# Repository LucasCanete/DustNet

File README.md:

# DustNet
Dust Measuring Station - Hochschule Osnabrück/Metropolia University

## Design Targets

Below is a list of circuits/features the schematic should include, regardless of if they are
part of the final design. 

The following [spreadsheet](https://docs.google.com/spreadsheets/d/1nFCJ1y3GU6Kr_cr4SUHvQ15Shn2fzcA_q6WiAYg45g8/edit?gid=0#gid=0)
is used to track some of the larger active components that are part of the electrical design.

- Battery cell (holder, connector)
- Cell Protection Circuit
- Cell Management Circuit (with MPPT)
- 3V3 Power rail
- Lora Powergate (res. GPIO + N-MOSFET)

## Final Design Circuits

TBD

## BOM

TBD

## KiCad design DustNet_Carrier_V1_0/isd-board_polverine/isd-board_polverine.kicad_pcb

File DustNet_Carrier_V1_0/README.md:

# DustNet
Dust Measuring Station - Hochschule Osnabrück/Metropolia University

## Board Features

- Dual-socket for Polverine and DFR1117 (mutually excl.)
- LiPo Protection Circuit
- 5V Power
- MPPT for charging
- USB-C for charging
- BME690 footprint (I2C)
- BMV080 connector (I2C)
- SPS30 connector (I2C)

## BOM

TBD

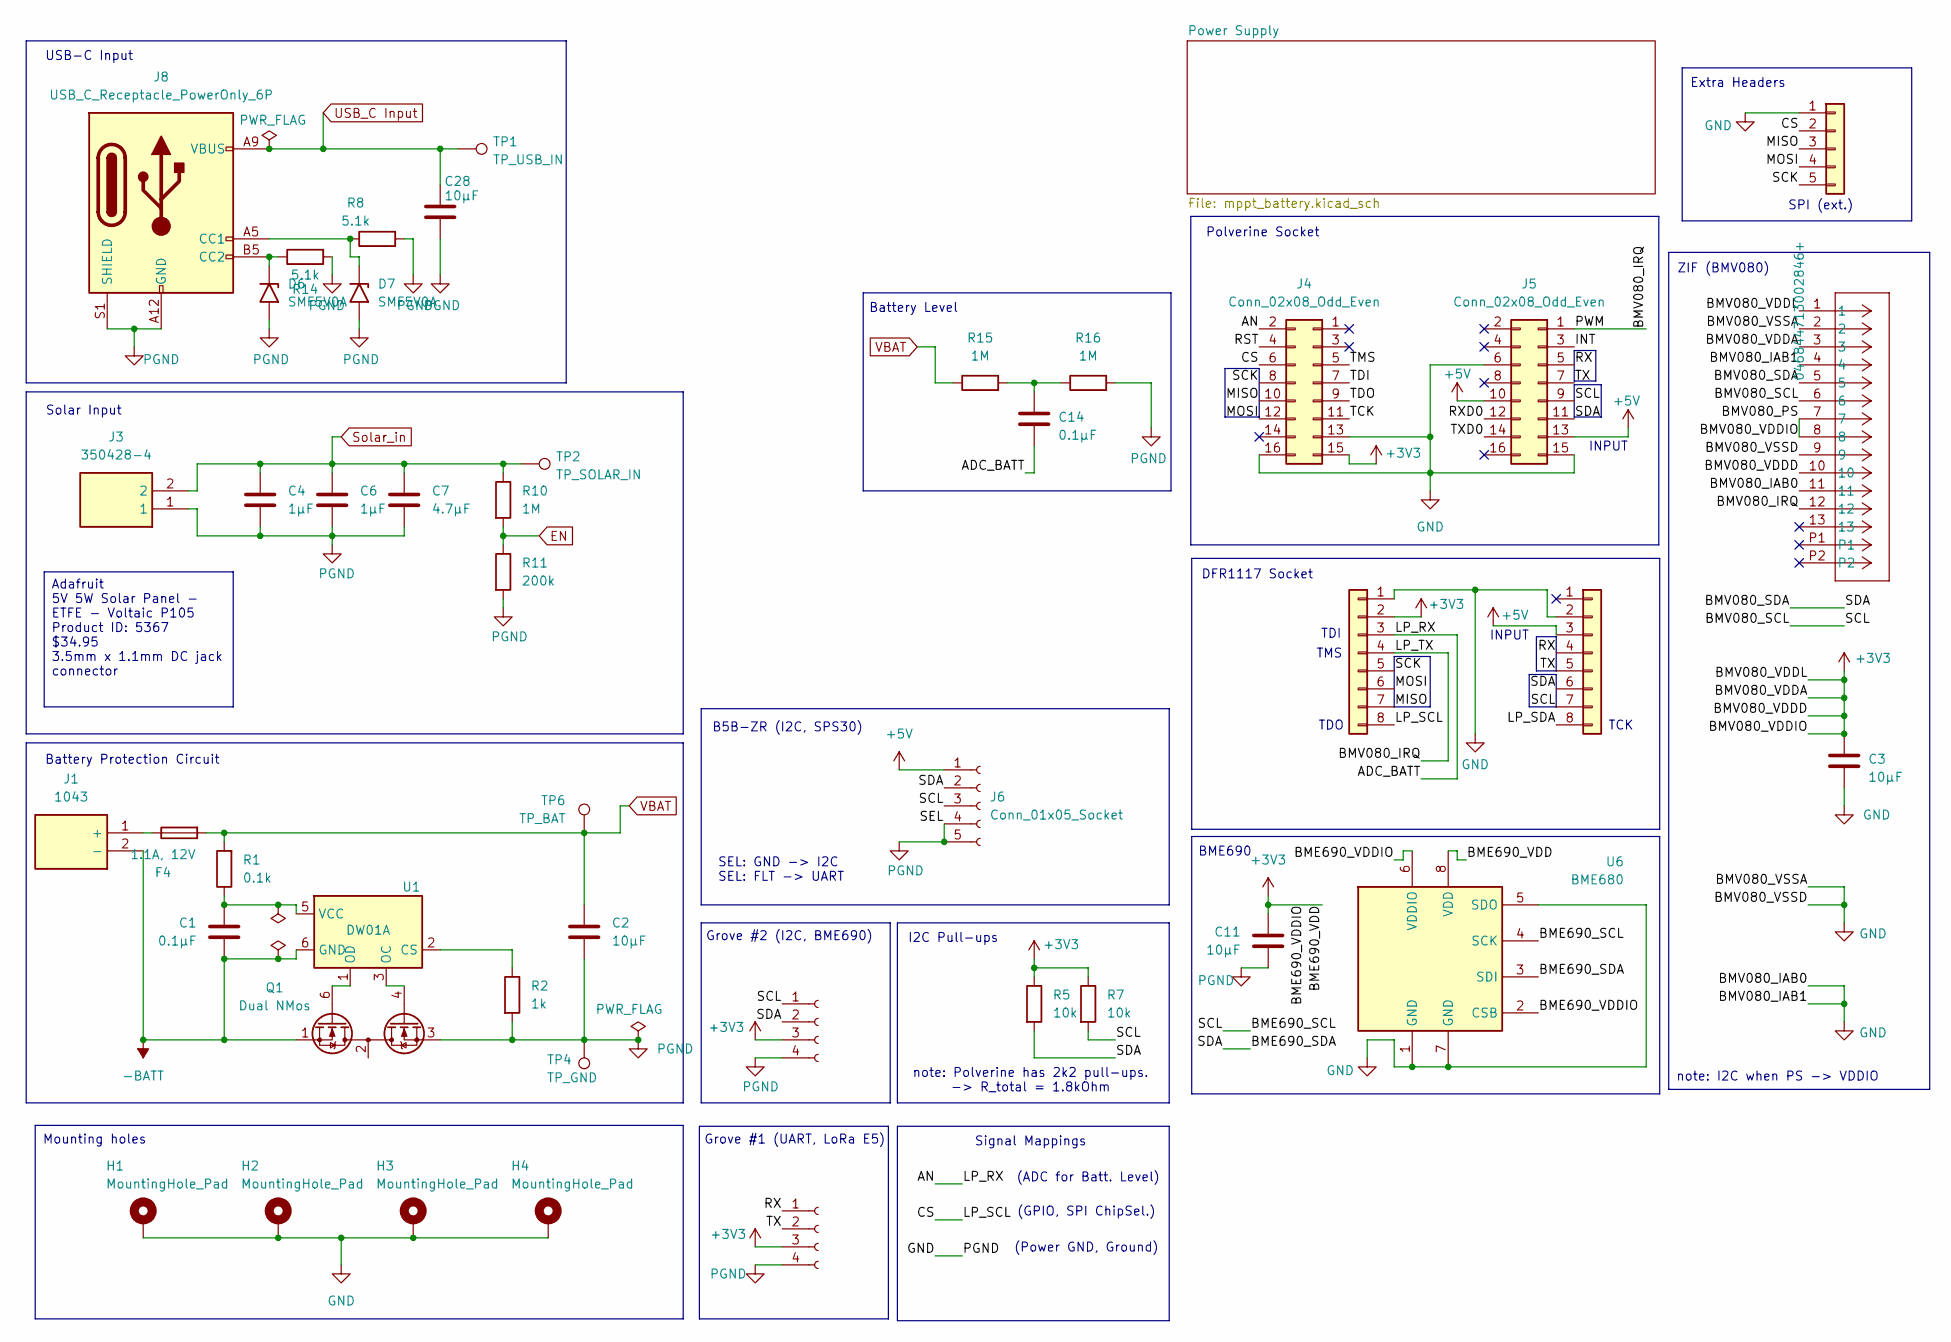
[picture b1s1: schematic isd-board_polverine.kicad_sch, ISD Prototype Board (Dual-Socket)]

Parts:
C1, C14: 0.1µF; C_0603_1608Metric; MPN 399-C0805C104K5RACTUCT-ND
C2, C3, C11: 10µF; C_0603_1608Metric; MPN GRM21BR61E106KA73K
C4, C6: 1µF; C_0603_1608Metric
C7: 4.7µF; C_0603_1608Metric
C28: 10µF; C_0603_1608Metric
D6, D7: SMF5V0A; D_SMF
F4: 1.1A, 12V; Fuse_1210_3225Metric_Pad1.42x2.65mm_HandSolder; MPN SMD1210B110TF
H1, H2, H3, H4: MountingHole_Pad; MountingHole_2.5mm_Pad_Via; MPN none
J1: 1043; Mouser Part Number 534-1043
J2, J9: Conn_01x04_Socket; NS-Tech_Grove_1x04_P2mm_Vertical; MPN 1597-1082-ND
J3: 350428-4; 3504284; Mouser Part Number 571-350428-4
J4, J5: Conn_02x08_Odd_Even; PinSocket_2x08_P2.54mm_Vertical; MPN 732-61301621821-ND
J6: Conn_01x05_Socket; JST_ZH_B5B-ZR_1x05_P1.50mm_Vertical; MPN B5B-ZR
J7, J10: Conn_01x08; PinSocket_1x08_P2.54mm_Vertical; MPN PPTC081LFBN-RC
J8: USB_C_Receptacle_PowerOnly_6P; USB_C_Receptacle_GCT_USB4125-xx-x-0190_6P_TopMnt_Horizontal; MPN USB4125-GF-A
J12: 5035661302; CON_5035661302_MOL; MPN 046844713002846+
J13: Conn_01x05; PinHeader_1x05_P2.54mm_Vertical; MPN ???
Q1: Dual NMos; SOT-23-6; MPN DMG9926UDMDICT-ND
R1: 0.1k; R_0603_1608Metric; MPN 541-100CCT-ND
R2: 1k; R_0603_1608Metric; MPN 10-ERJ-HP6J102VCT-ND
R5, R7: 10k; R_0603_1608Metric; MPN 541-4163-1-ND
R8, R14: 5.1k; R_0603_1608Metric; MPN 311-5.1KARCT-ND
R10: 1M; R_0603_1608Metric
R11: 200k; R_0603_1608Metric
R15, R16: 1M; R_0603_1608Metric; MPN 408-RG2012P-105-B-T5CT-ND
TP1: TP_USB_IN; TestPoint_Pad_1.5x1.5mm; MPN none
TP2: TP_SOLAR_IN; TestPoint_Pad_1.5x1.5mm; MPN none
TP4: TP_GND; TestPoint_Pad_D1.0mm; MPN none
TP6: TP_BAT; TestPoint_Pad_1.5x1.5mm; MPN none
U1: DW01A; SOT-23-6_Handsoldering; MPN DW01A
U6: BME680; Bosch_LGA-8_3x3mm_P0.8mm_ClockwisePinNumbering; MPN BME690

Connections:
+3V3: C3.1, C11.1, J2.3, J4.15, J9.3, J10.2, J12.1, J12.3, J12.7, J12.8, J12.10, R5.1, R7.1, U6.2 (CSB), U6.6 (VDDIO), U6.8 (VDD); also elsewhere on the board
+5V: J5.10, J5.13, J6.1, J7.3; also elsewhere on the board
-BATT: C1.2, J1.2 (-), Q1.1 (D1), U1.6 (GND)
/ADC_BATT: C14.2, J4.2, J10.3
/BME690_SCL: J2.1, J5.9, J6.3, J7.7, J12.6, R7.2, U6.4 (SCK)
/BME690_SDA: J2.2, J5.11, J6.2, J7.6, J12.5, R5.2, U6.3 (SDI)
/BMV080_IRQ: J5.1, J10.4, J12.12
/CS: J4.6, J10.8, J13.2
/INT: J5.3
/LP_SDA: J7.8
/MISO: J4.10, J10.7, J13.3
/MOSI: J4.12, J10.6, J13.4
/RST: J4.4
/RX: J5.5, J7.4, J9.1
/RXD0: J5.12
/SCK: J4.8, J10.5, J13.5
/TCK: J4.11
/TDI: J4.7
/TDO: J4.9
/TMS: J4.5
/TX: J5.7, J7.5, J9.2
/TXD0: J5.14
EN: R10.2, R11.1; also elsewhere on the board
unnamed: C14.1, R15.2, R16.1
unnamed: D6.1 (A1), J8.B5 (CC2), R14.1
unnamed: D7.1 (A1), J8.A5 (CC1), R8.1
unnamed: F4.1, J1.1 (+)
unnamed: Q1.6 (G1), U1.1 (OD)
unnamed: Q1.4 (G2), U1.3 (OC)
unnamed: Q1.2 (S1/D2), Q1.5 (S1/D2)
unnamed: R2.1, U1.2 (CS)
unnamed: C1.1, R1.1, U1.5 (VCC)
Solar_in: C4.1, C6.1, C7.1, J3.2, R10.1, TP2.1; also elsewhere on the board
USB_C Input: C28.1, J8.A9 (VBUS), J8.B9 (VBUS), TP1.1; also elsewhere on the board
VBAT: C2.1, F4.2, R1.2, R15.1, TP6.1; also elsewhere on the board

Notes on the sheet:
INPUT
B5B-ZR (I2C, SPS30)
Polverine Socket
TDO
I2C Pull-ups
Battery Level
note: Polverine has 2k2 pull-ups. -> R_total = 1.8kOhm
Solar Input
DFR1117 Socket
Mounting holes
TDI
BME690
(GPIO, SPI ChipSel.)
TCK
Extra Headers
(ADC for Batt. Level)
(Power GND, Ground)
USB-C Input
ZIF (BMV080)
Grove #1 (UART, LoRa E5)
SPI (ext.)
note: I2C when PS -> VDDIO
Battery Protection Circuit
Signal Mappings
TMS
SEL: GND -> I2C SEL: FLT -> UART
Grove #2 (I2C, BME690)
Adafruit 5V 5W Solar Panel - ETFE - Voltaic P105 Product ID: 5367 $34.95 3.5mm x 1.1mm DC jack connector

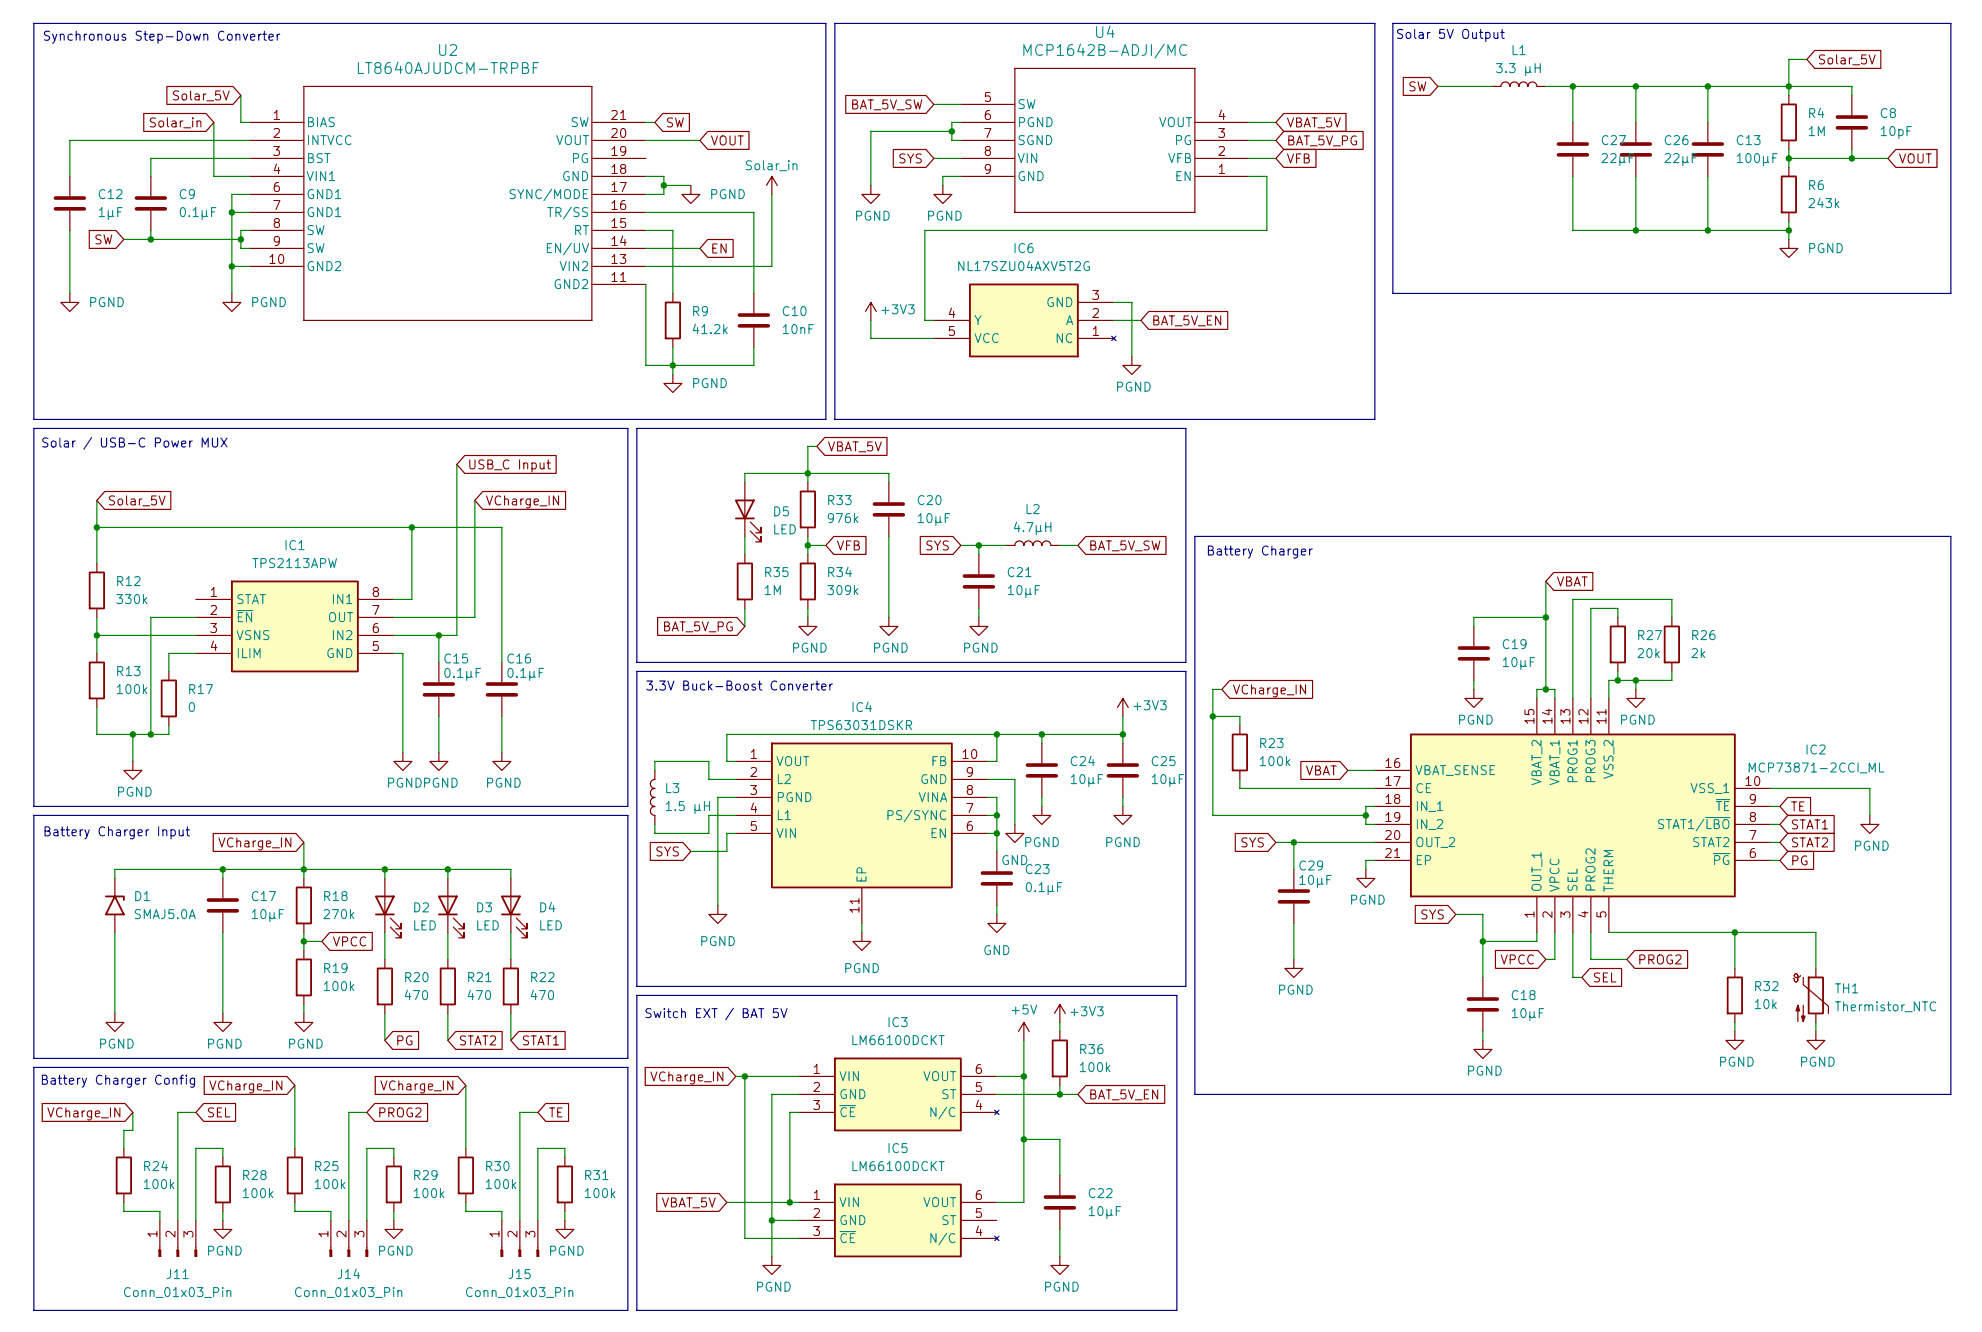
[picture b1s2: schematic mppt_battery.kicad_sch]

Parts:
C8: 10pF; C_0603_1608Metric
C9, C15, C16, C23: 0.1µF; C_0603_1608Metric
C10: 10nF; C_0603_1608Metric
C12: 1µF; C_0603_1608Metric
C13: 100µF; C_1206_3216Metric
C17, C18, C19, C20, C21, C22, C24, C25, C29: 10µF; C_0603_1608Metric
C26, C27: 22µF; C_1206_3216Metric
D1: SMAJ5.0A; D_SMA
D2, D3, D4, D5: LED; KRDELPS122VGVI23H3Q4
IC1: TPS2113APW; SOP65P640X120-8N; Mouser Part Number 595-TPS2113APW
IC2: MCP73871-2CCI_ML; QFN50P400X400X100-21N-D; Mouser Part Number 579-MCP73871-2CCI/ML
IC3, IC5: LM66100DCKT; SOT65P210X110-6N; Mouser Part Number 595-LM66100DCKT
IC4: TPS63031DSKR; SON50P250X250X80-11N-D; Mouser Part Number 595-TPS63031DSKR
IC6: NL17SZU04AXV5T2G; Manufacturer_Part_Number NL17SZU04AXV5T2G
J11, J14, J15: Conn_01x03_Pin; PinHeader_1x03_P2.54mm_Vertical
L1: 3.3 µH; XFL4020332MEC
L2: 4.7µH; XFL4020332MEC
L3: 1.5 µH; XFL4020332MEC
R4, R35: 1M; R_0603_1608Metric
R6: 243k; R_0603_1608Metric
R9: 41.2k; R_0603_1608Metric
R12: 330k; R_0603_1608Metric
R13, R19, R23, R24, R25, R28, R29, R30, R31, R36: 100k; R_0603_1608Metric
R17: 0; R_0603_1608Metric
R18: 270k; R_0603_1608Metric
R20, R21, R22: 470; R_0603_1608Metric
R26: 2k; R_0603_1608Metric
R27: 20k; R_0603_1608Metric
R32: 10k; R_0603_1608Metric
R33: 976k; R_0603_1608Metric
R34: 309k; R_0603_1608Metric
TH1: Thermistor_NTC; R_Axial_DIN0204_L3.6mm_D1.6mm_P1.90mm_Vertical
U2: LT8640AJUDCM-TRPBF; UDCM_05-08-7030_ADI
U4: MCP1642B-ADJI/MC; DFN8_MC_MCH

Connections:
+3V3: C24.1, C25.1, IC4.1 (VOUT), IC4.10 (FB), IC6.5 (VCC), R36.1; also elsewhere on the board
+5V: C22.1, IC3.6 (VOUT), IC5.6 (VOUT); also elsewhere on the board
BAT_5V_EN: IC3.5 (ST), IC6.2 (A), R36.2
BAT_5V_PG: R35.2, U4.3 (PG)
BAT_5V_SW: L2.2, U4.5 (SW)
EN: U2.14 (EN/UV); also elsewhere on the board
unnamed: D2.1 (K), R20.1
unnamed: D3.1 (K), R21.1
unnamed: D4.1 (K), R22.1
unnamed: D5.1 (K), R35.1
unnamed: IC1.4 (ILIM), R17.1
unnamed: IC1.3 (VSNS), R12.2, R13.1
unnamed: IC2.17 (CE), R23.2
unnamed: IC2.13 (PROG1), R26.1
unnamed: IC2.12 (PROG3), R27.1
unnamed: IC2.5 (THERM), R32.1, TH1.1
unnamed: C23.1, IC4.6 (EN), IC4.7 (PS/SYNC), IC4.8 (VINA)
unnamed: IC4.4 (L1), L3.1
unnamed: IC4.2 (L2), L3.2
unnamed: IC6.4 (Y), U4.1 (EN)
unnamed: J11.1, R24.2
unnamed: J11.3, R28.1
unnamed: J14.1, R25.2
unnamed: J14.3, R29.1
unnamed: J15.1, R30.2
unnamed: J15.3, R31.1
unnamed: C9.1, U2.3 (BST)
unnamed: C12.1, U2.2 (INTVCC)
unnamed: R9.1, U2.15 (RT)
unnamed: C10.1, U2.16 (TR/SS)
PG: IC2.6 (~PG), R20.2
PROG2: IC2.4 (PROG2), J14.2
SEL: IC2.3 (SEL), J11.2
STAT1: IC2.8 (STAT1/~LBO), R22.2
STAT2: IC2.7 (STAT2), R21.2
SW: C9.2, L1.1, U2.8 (SW), U2.9 (SW), U2.21 (SW)
SYS: C18.1, C21.1, C29.1, IC2.1 (OUT_1), IC2.20 (OUT_2), IC4.5 (VIN), L2.1, U4.8 (VIN)
Solar_5V: C8.1, C13.1, C16.1, C26.1, C27.1, IC1.8 (IN1), L1.2, R4.1, R12.1, U2.1 (BIAS)
Solar_in: U2.4 (VIN1), U2.13 (VIN2); also elsewhere on the board
TE: IC2.9 (~TE), J15.2
USB_C Input: C15.1, IC1.6 (IN2); also elsewhere on the board
VBAT: C19.1, IC2.14 (VBAT_1), IC2.15 (VBAT_2), IC2.16 (VBAT_SENSE); also elsewhere on the board
VBAT_5V: C20.1, D5.2 (A), IC3.3 (~CE), IC5.1 (VIN), R33.1, U4.4 (VOUT)
VCharge_IN: C17.1, D1.1 (A1), D2.2 (A), D3.2 (A), D4.2 (A), IC1.7 (OUT), IC2.18 (IN_1), IC2.19 (IN_2), IC3.1 (VIN), IC5.3 (~CE), R18.1, R23.1, R24.1, R25.1, R30.1
VFB: R33.2, R34.1, U4.2 (VFB)
VOUT: C8.2, R4.2, R6.1, U2.20 (VOUT)
VPCC: IC2.2 (VPCC), R18.2, R19.1

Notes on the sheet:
Solar 5V Output
3.3V Buck-Boost Converter
Solar / USB-C Power MUX
Battery Charger
Switch EXT / BAT 5V
Synchronous Step-Down Converter
Battery Charger Config
Battery Charger Input

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
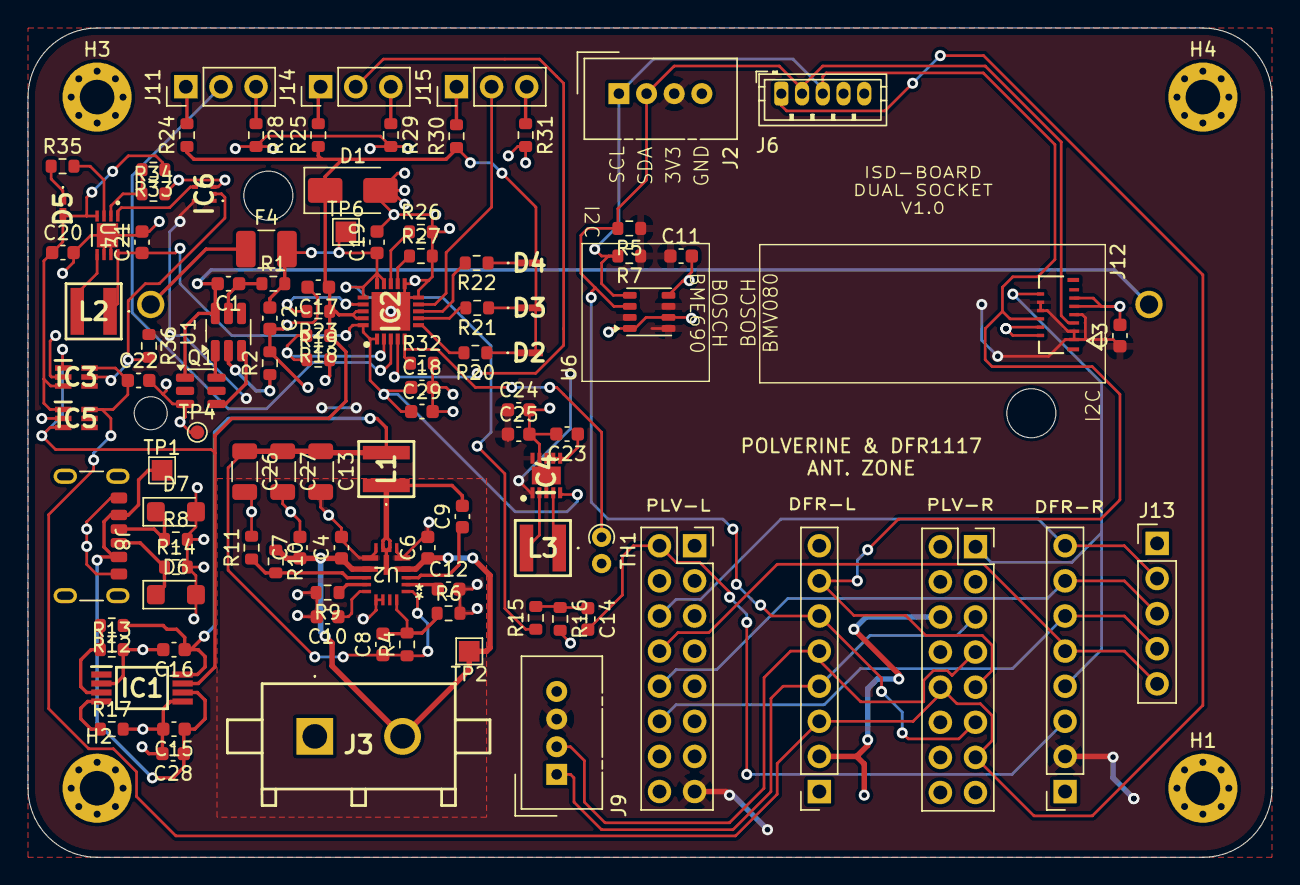
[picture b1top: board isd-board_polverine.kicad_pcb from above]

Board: 2 copper layers, 90.0 x 60.0 mm, 109 parts (1 on the bottom side), 68 nets.

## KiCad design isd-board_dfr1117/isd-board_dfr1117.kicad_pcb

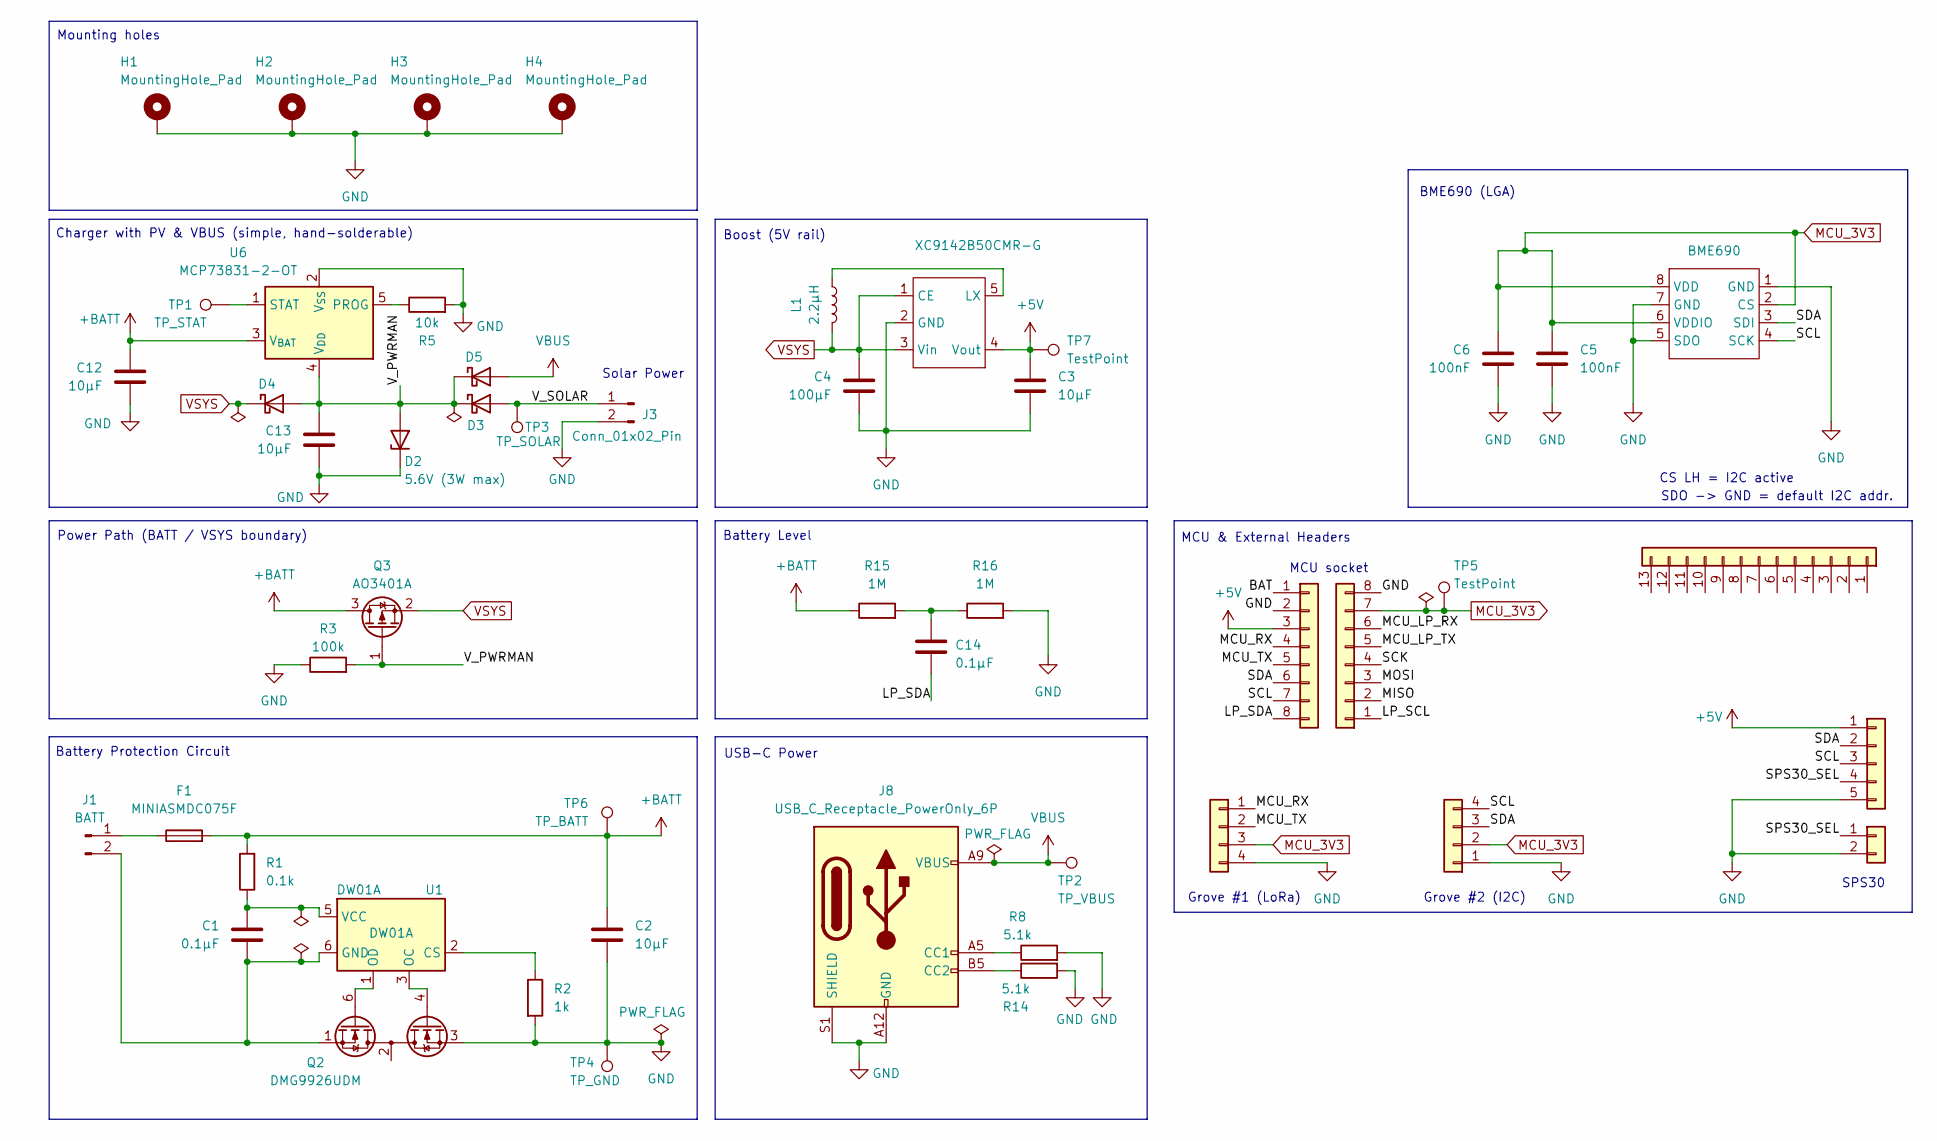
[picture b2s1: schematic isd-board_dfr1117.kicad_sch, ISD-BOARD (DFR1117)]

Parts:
C1, C14: 0.1µF; C_0805_2012Metric_Pad1.18x1.45mm_HandSolder
C2, C3, C12, C13: 10µF; C_0805_2012Metric_Pad1.18x1.45mm_HandSolder
C4: 100µF; CP_Radial_D5.0mm_P2.50mm
C5, C6: 100nF
D2: 5.6V (3W max); D_SMB_Handsoldering; MPN 1SMB5919BT3G
D3, D4, D5: D_Schottky; D_DO-41_SOD81_P10.16mm_Horizontal
F1: MINIASMDC075F; Fuse_1812_4532Metric_Pad1.30x3.40mm_HandSolder
H1, H2, H3, H4: MountingHole_Pad; MountingHole_2.5mm_Pad_Via
J1: BATT; JST_PH_S2B-PH-K_1x02_P2.00mm_Horizontal
J2, J4: Conn_01x08; PinSocket_1x08_P2.54mm_Vertical
J3: Conn_01x02_Pin; JST_PH_S2B-PH-K_1x02_P2.00mm_Horizontal
J5, J6: Conn_01x04; NS-Tech_Grove_1x04_P2mm_Vertical
J7: Conn_01x05; JST_ZH_B5B-ZR_1x05_P1.50mm_Vertical
J8: USB_C_Receptacle_PowerOnly_6P; USB_C_Receptacle_GCT_USB4125-xx-x-0190_6P_TopMnt_Horizontal
J9: Conn_01x02
J10: Conn_01x13
L1: 2.2µH; L_Bourns-SRN4018; MPN SRN4018-2R2M
Q2: DMG9926UDM; SOT-23-6
Q3: AO3401A; SOT-23_Handsoldering
R1: 0.1k; R_0805_2012Metric_Pad1.20x1.40mm_HandSolder
R2: 1k; R_0805_2012Metric_Pad1.20x1.40mm_HandSolder
R3: 100k; R_0805_2012Metric_Pad1.20x1.40mm_HandSolder
R5: 10k; R_0805_2012Metric_Pad1.20x1.40mm_HandSolder
R8, R14: 5.1k; R_0805_2012Metric_Pad1.20x1.40mm_HandSolder
R15, R16: 1M; R_0805_2012Metric_Pad1.20x1.40mm_HandSolder
TP1: TP_STAT; TestPoint_Pad_D1.0mm
TP2: TP_VBUS; TestPoint_Pad_D1.0mm
TP3: TP_SOLAR; TestPoint_Pad_D1.0mm
TP4: TP_GND; TestPoint_Pad_D1.0mm
TP5, TP7: TestPoint; TestPoint_Pad_D1.0mm
TP6: TP_BATT; TestPoint_Pad_D1.0mm
U1: DW01A; SOT-23-6_Handsoldering
U2: XC9142B50CMR-G; SOT-23-5_HandSoldering
U3: BME690; Bosch_LGA-8_2.5x2.5mm_P0.65mm_ClockwisePinNumbering
U6: MCP73831-2-OT; SOT-23-5_HandSoldering; MPN MCP73831T-2DCI/OT

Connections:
+5V: C3.1, J2.3, J7.1, TP7.1, U2.4 (Vout)
+BATT: C2.1, C12.1, F1.2, Q3.3 (D), R1.2, R15.1, TP6.1, U6.3 (V_{BAT})
/BAT: J2.1
/LP_SCL: J4.1
/LP_SDA: C14.2, J2.8
/MCU_LP_RX: J4.6
/MCU_LP_TX: J4.5
/MCU_RX: J2.4, J5.1
/MCU_TX: J2.5, J5.2
/MISO: J4.2
/MOSI: J4.3
/SCK: J4.4
/SCL: J2.7, J6.4, J7.3, U3.4 (SCK)
/SDA: J2.6, J6.3, J7.2, U3.3 (SDI)
/SPS30_SEL: J7.4, J9.1
/V_PWRMAN: C13.1, D2.2 (A), D3.1 (K), D4.2 (A), D5.1 (K), Q3.1 (G), R3.2, U6.4 (V_{DD})
/V_SOLAR: D3.2 (A), J3.1, TP3.1
GND: C2.2, C3.2, C4.2, C5.2, C6.1, C12.2, C13.2, D2.1 (K), H1.1, H2.1, H3.1, H4.1, J2.2, J3.2, J4.8, J5.4, J6.1, J7.5, J8.A12 (GND), J8.B12 (GND), J8.S1 (SHIELD), J9.2, Q2.3 (S2), R2.2, R3.1, R5.2, R8.2, R14.2, R16.2, TP4.1, U2.2 (GND), U3.1 (GND), U3.5 (SDO), U3.7 (GND), U6.2 (V_{SS})
MCU_3V3: C5.1, C6.2, J4.7, J5.3, J6.2, TP5.1, U3.2 (CS), U3.6 (VDDIO), U3.8 (VDD)
unnamed: C14.1, R15.2, R16.1
unnamed: F1.1, J1.1
unnamed: C1.2, J1.2, Q2.1 (D1), U1.6 (GND)
unnamed: J8.A5 (CC1), R8.1
unnamed: J8.B5 (CC2), R14.1
unnamed: Q2.6 (G1), U1.1 (OD)
unnamed: Q2.4 (G2), U1.3 (OC)
unnamed: Q2.2 (S1/D2), Q2.5 (S1/D2)
unnamed: R2.1, U1.2 (CS)
unnamed: C1.1, R1.1, U1.5 (VCC)
unnamed: L1.2, U2.5 (LX)
unnamed: R5.1, U6.5 (PROG)
unnamed: TP1.1, U6.1 (STAT)
VBUS: D5.2 (A), J8.A9 (VBUS), J8.B9 (VBUS), TP2.1
VSYS: C4.1, D4.1 (K), L1.1, Q3.2 (S), U2.1 (CE), U2.3 (Vin)

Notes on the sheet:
Charger with PV & VBUS (simple, hand-solderable)
Battery Level
Grove #1 (LoRa)
CS LH = I2C active
Mounting holes
MCU & External Headers
MCU socket
SPS30
Solar Power
Boost (5V rail)
SDO -> GND = default I2C addr.
Power Path (BATT / VSYS boundary)
Battery Protection Circuit
Grove #2 (I2C)
USB-C Power
BME690 (LGA)

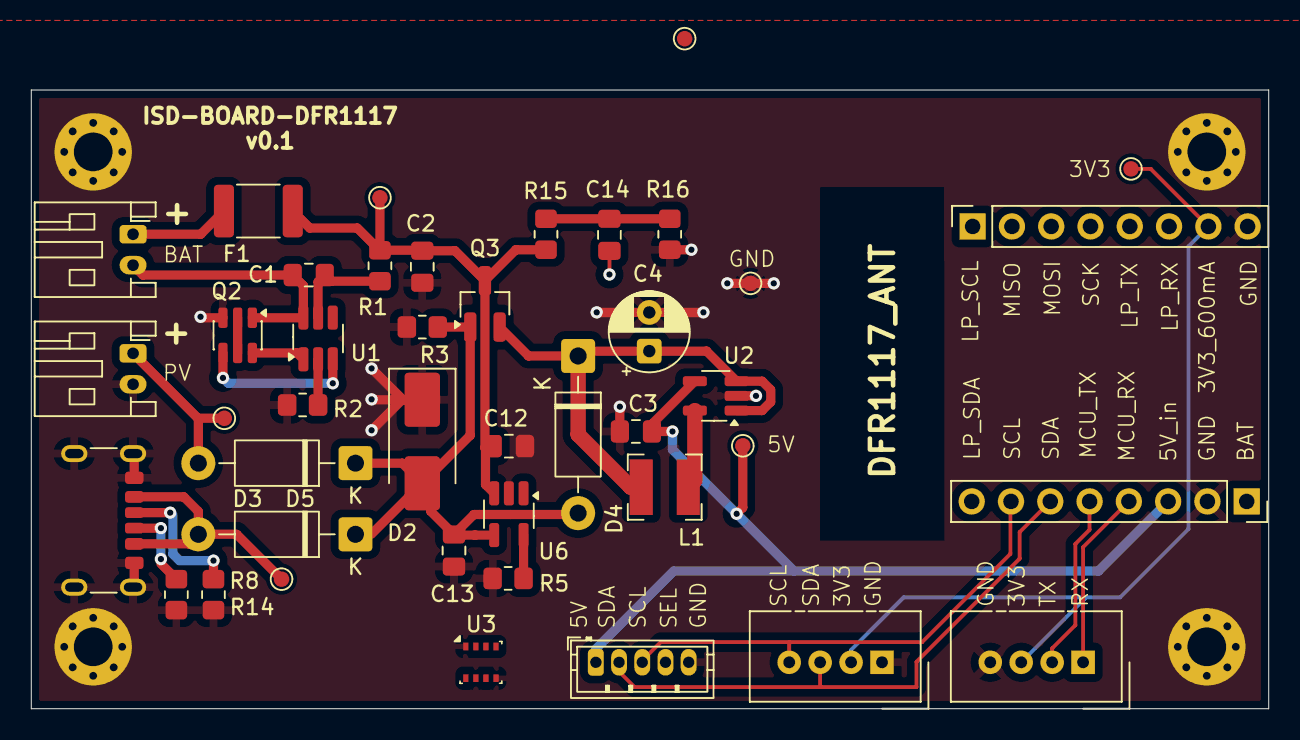
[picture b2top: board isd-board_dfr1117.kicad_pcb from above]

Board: 2 copper layers, 80.0 x 40.0 mm, 46 parts (0 on the bottom side), 26 nets.

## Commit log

2025-12-05 Added Datasheets dir
2025-12-05 upload test
2025-12-05 update: README.md (add some design targets)
2025-12-05 add: gitignore (ignore kicad locks, backups)
2025-12-05 add: kicad library tree
2025-12-05 update: README.md (BOM, targets)
2025-12-05 add: polverine-carrier project directory
2025-12-05 update: isd-polverine-carrier/sch (add battery protection circuit)
2025-12-07 Added first charger controller prototype
2026-01-07 update: battery protection circuit (assign components, change to hand-solderable footprints)
2026-01-07 add: LDO (3V3)
2026-01-07 add: PV charger (simple, hand-solderable)
2026-01-07 add: Polverine mikroBUS headers
2026-01-08 add: USB-port for charging, carrier headers, battery monitoring
2026-01-13 Added P Mos to solar charger controller for load sharing
2026-01-19 add: isd-board (DFR1117 version, non-MPTT)
2026-01-19 add: isd-board_polverine (MPTT version base)
2026-01-19 update: battery protection circuit (compact placement)
2026-01-28 update: dual-socket sch/pcb (polverine socket, dfr1117 socket, grove-conn, zif-conn (bmv080), lga 3x3mm (bme690), b5b-zr (sps30))
2026-01-28 update: README.md (to reflect current project goals)
2026-01-29 Added resistor values to MPPT and connection to Battery protection
2026-02-04 lora power gate initial commit
2026-02-05 update: sch/pcb (pin routing, bmv690/bmv080 footprints, power switch ic)
2026-02-15 New Schematic with complete Power Supply
2026-02-15 added bill of materials with mouser number parts
2026-02-16 Here the latest complete Version including PCB Design
